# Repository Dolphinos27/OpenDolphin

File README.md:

# OpenDolphin
🐬 OpenDolphin: An open-source, DIY PCB clone of Flipper Zero.

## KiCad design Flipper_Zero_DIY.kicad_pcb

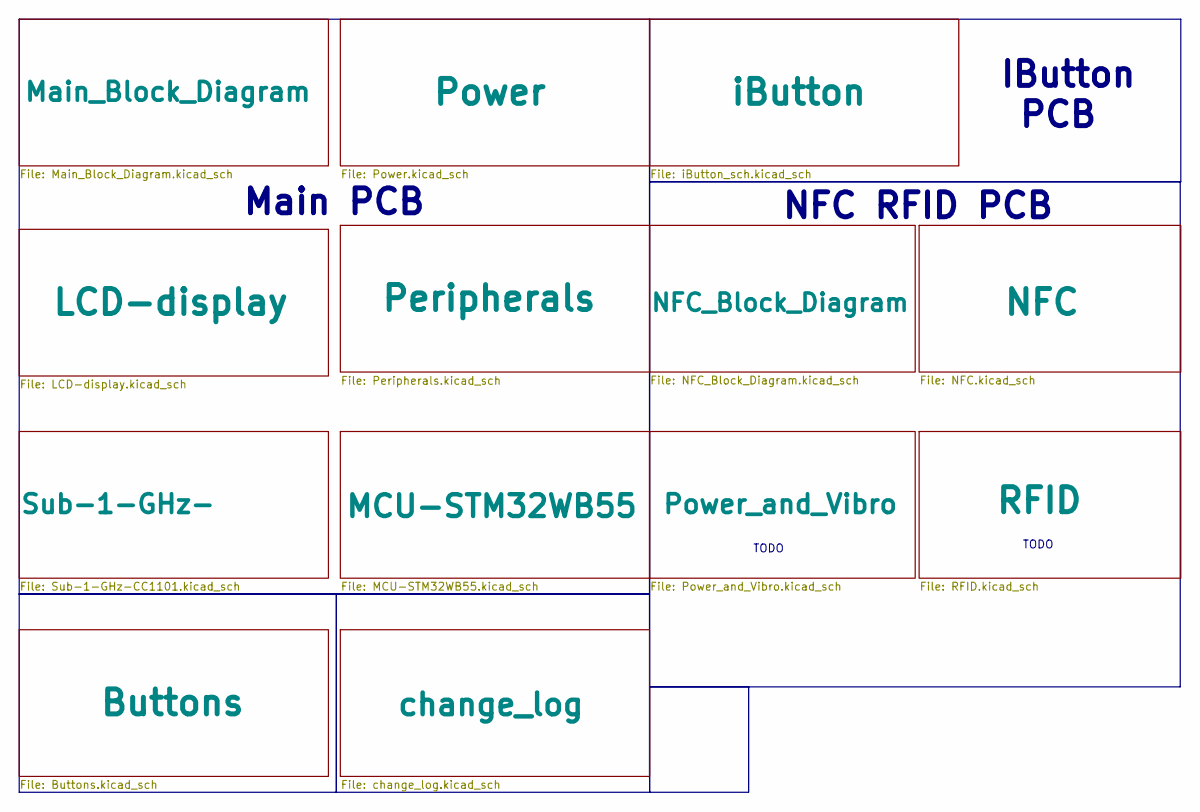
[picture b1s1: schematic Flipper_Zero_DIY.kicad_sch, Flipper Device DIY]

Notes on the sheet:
TODO
IButton PCB
Main PCB
NFC RFID PCB

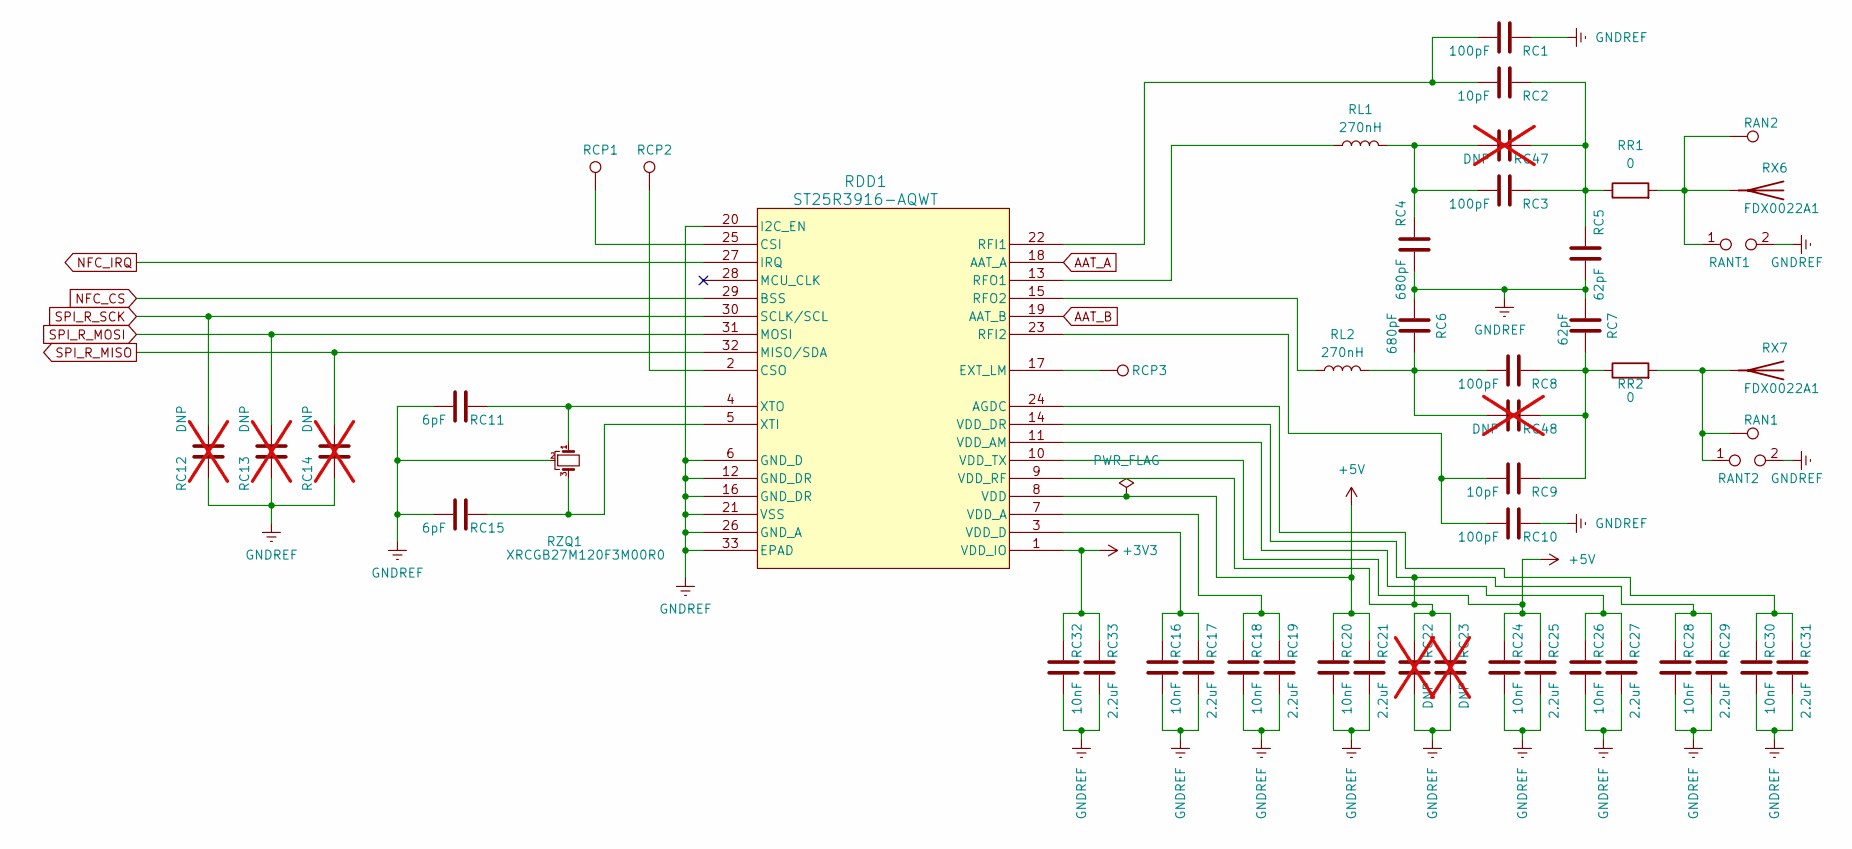
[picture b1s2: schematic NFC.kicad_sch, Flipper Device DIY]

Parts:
RC1, RC3, RC8, RC10: 100pF; C_0603_1608Metric
RC2, RC9: 10pF; C_0603_1608Metric
RC4, RC6: 680pF; C_0603_1608Metric
RC5, RC7: 62pF; C_0603_1608Metric
RC11, RC15: 6pF; C_0603_1608Metric
RC12, RC13, RC14, RC22, RC23, RC47, RC48: DNP; C_0603_1608Metric; not fitted
RC16, RC18, RC20, RC24, RC26, RC28, RC30, RC32: 10nF; C_0603_1608Metric
RC17, RC19, RC21, RC25, RC27, RC29, RC31, RC33: 2.2uF; C_0603_1608Metric
RDD1: ST25R3916-AQWT; VFQFPN32_5X5_WETTABLE_STM
RL1, RL2: 270nH; L_0603_1608Metric
RR1, RR2: 0; R_0603_1608Metric
RX6, RX7: FDX0022A1; R_0603_1608Metric
RZQ1: XRCGB27M120F3M00R0; Crystal_SMD_3225-4Pin_3.2x2.5mm
TP62: RCP1; TestPoint_Pad_D1.0mm
TP63: RCP2; TestPoint_Pad_D1.0mm
TP64: RAN2; TestPoint_Pad_D1.0mm
TP65: RANT1; SolderJumper-2_P1.3mm_Open_RoundedPad1.0x1.5mm
TP66: RAN1; TestPoint_Pad_D1.0mm
TP67: RANT2; SolderJumper-2_P1.3mm_Open_RoundedPad1.0x1.5mm
TP68: RCP3; TestPoint_Pad_D1.0mm

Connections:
+5V: RC20.2, RC21.2, RC24.2, RC25.2, RDD1.8 (VDD), RDD1.10 (VDD_TX); also elsewhere on the board
AAT_A: RDD1.18 (AAT_A)
AAT_B: RDD1.19 (AAT_B)
GND: RC1.2, RC4.1, RC5.1, RC6.2, RC7.2, RC10.2, RC11.1, RC12.2, RC13.2, RC14.2, RC15.1, RC16.1, RC17.1, RC18.1, RC19.1, RC20.1, RC21.1, RC22.1, RC23.1, RC24.1, RC25.1, RC26.1, RC27.1, RC28.1, RC29.1, RC30.1, RC31.1, RC32.1, RC33.1, RDD1.6 (GND_D), RDD1.12 (GND_DR), RDD1.16 (GND_DR), RDD1.20 (I2C_EN), RDD1.21 (VSS), RDD1.26 (GND_A), RDD1.33 (EPAD), RZQ1.2, TP65.2, TP67.2; also elsewhere on the board
NFC_CS: RDD1.29 (BSS); also elsewhere on the board
NFC_IRQ: RDD1.27 (IRQ)
unnamed: RC2.2, RC3.2, RC5.2, RC47.2, RR1.1
unnamed: RC3.1, RC4.2, RC47.1, RL1.2
unnamed: RC6.1, RC8.1, RC48.1, RL2.2
unnamed: RC7.1, RC8.2, RC9.2, RC48.2, RR2.1
unnamed: RC30.2, RC31.2, RDD1.24 (AGDC)
unnamed: RDD1.25 (CSI), TP62.1
unnamed: RDD1.2 (CSO), TP63.1
unnamed: RDD1.17 (EXT_LM), TP68.1
unnamed: RC1.1, RC2.1, RDD1.22 (RFI1)
unnamed: RC9.1, RC10.1, RDD1.23 (RFI2)
unnamed: RDD1.13 (RFO1), RL1.1
unnamed: RDD1.15 (RFO2), RL2.1
unnamed: RC18.2, RC19.2, RDD1.7 (VDD_A)
unnamed: RC26.2, RC27.2, RDD1.11 (VDD_AM)
unnamed: RC16.2, RC17.2, RDD1.3 (VDD_D)
unnamed: RC22.2, RC23.2, RC28.2, RC29.2, RDD1.9 (VDD_RF), RDD1.14 (VDD_DR)
unnamed: RC15.2, RDD1.5 (XTI), RZQ1.3
unnamed: RC11.2, RDD1.4 (XTO), RZQ1.1
unnamed: RR1.2, RX6.1 (A), TP64.1, TP65.1
unnamed: RR2.2, RX7.1 (A), TP66.1, TP67.1
SPI_R_MISO: RC14.1, RDD1.32 (MISO/SDA); also elsewhere on the board
SPI_R_MOSI: RC13.1, RDD1.31 (MOSI); also elsewhere on the board
SPI_R_SCK: RC12.1, RDD1.30 (SCLK/SCL); also elsewhere on the board

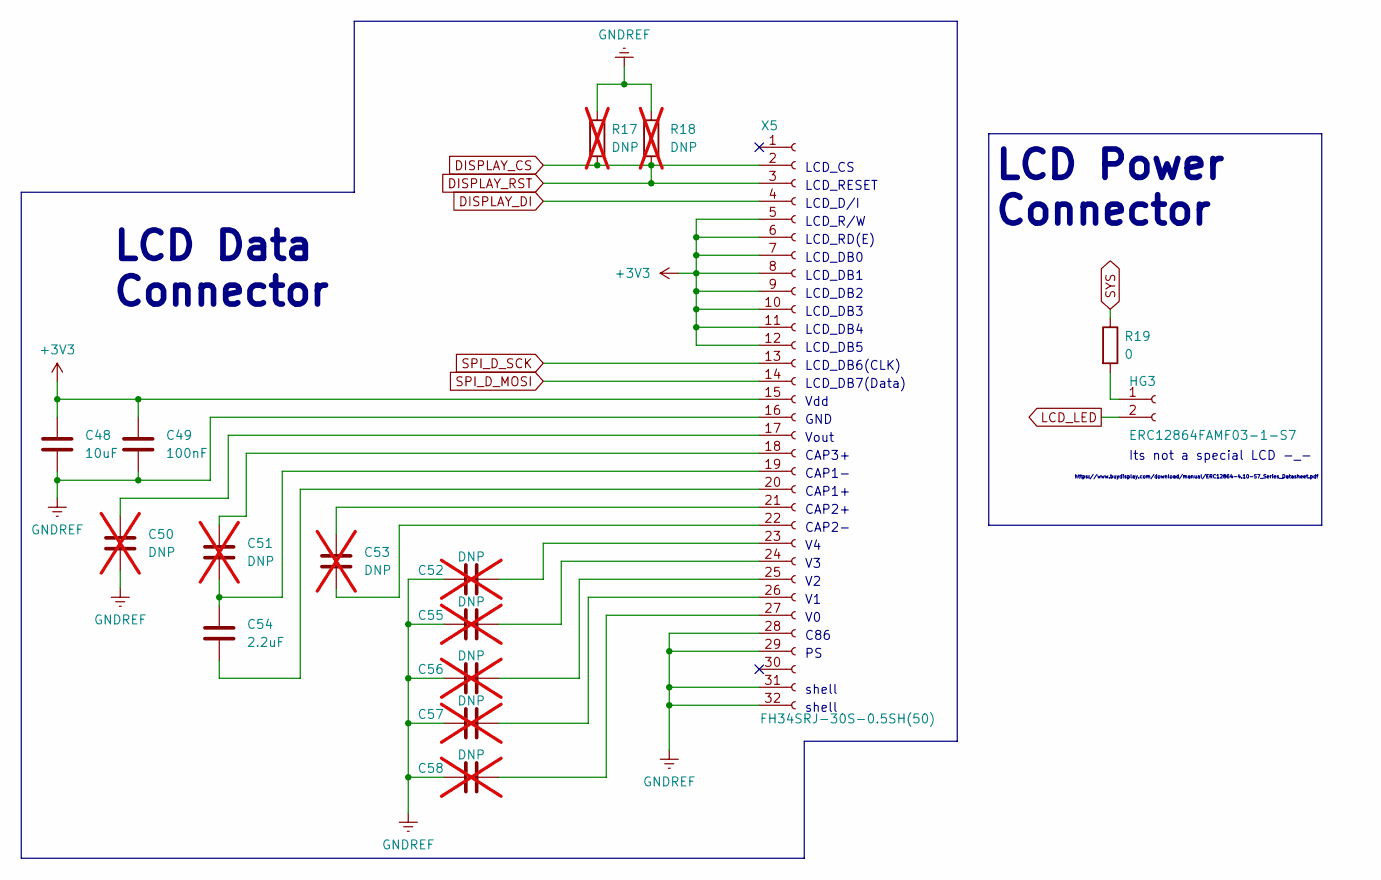
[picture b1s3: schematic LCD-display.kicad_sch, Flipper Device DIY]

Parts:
C48: 10uF; C_0603_1608Metric
C49: 100nF; C_0402_1005Metric
C50, C51, C52, C53, C55, C56, C57, C58: DNP; C_0402_1005Metric; not fitted
C54: 2.2uF; C_0402_1005Metric
HG3: ERC12864FAMF03-1-S7; PinHeader_1x02_P2.00mm_Vertical_SMD_Pin1Left
R17, R18: DNP; R_0402_1005Metric; not fitted
R19: 0; R_0402_1005Metric
X5: FH34SRJ-30S-0.5SH(50); CONN30x1_FH34SRJ-30S-0.5SH50_HIR

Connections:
DISPLAY_CS: R17.2, R18.2, X5.2, X5.3; also elsewhere on the board
DISPLAY_DI: X5.4; also elsewhere on the board
GND: C48.2, C49.2, C50.2, C52.1, C55.1, C56.1, C57.1, C58.1, R17.1, R18.1, X5.16, X5.28, X5.29, X5.31, X5.32; also elsewhere on the board
LCD_LED: HG3.2; also elsewhere on the board
unnamed: HG3.1, R19.2
unnamed: C50.1, X5.17
unnamed: C51.1, X5.18
unnamed: C51.2, C54.1, X5.19
unnamed: C54.2, X5.20
unnamed: C53.1, X5.21
unnamed: C53.2, X5.22
unnamed: C52.2, X5.23
unnamed: C55.2, X5.24
unnamed: C56.2, X5.25
unnamed: C57.2, X5.26
unnamed: C58.2, X5.27
SPI_D_MOSI: X5.13, X5.14; also elsewhere on the board
SYS: R19.1; also elsewhere on the board

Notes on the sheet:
LCD_DB2
LCD_D/I
LCD_DB0
LCD_RESET
LCD Data Connector
Vdd
LCD_DB6(CLK)
C86
GND
LCD_DB7(Data)
LCD_RD(E)
LCD_DB1
CAP1+
LCD_CS
CAP2-
shell
Vout
LCD_R/W
Its not a special LCD -_-
CAP3+
LCD Power Connector
CAP1-
https://www.buydisplay.com/download/manual/ERC12864-4.10-S7_Series_Datasheet.pdf
LCD_DB4
CAP2+
LCD_DB5
LCD_DB3

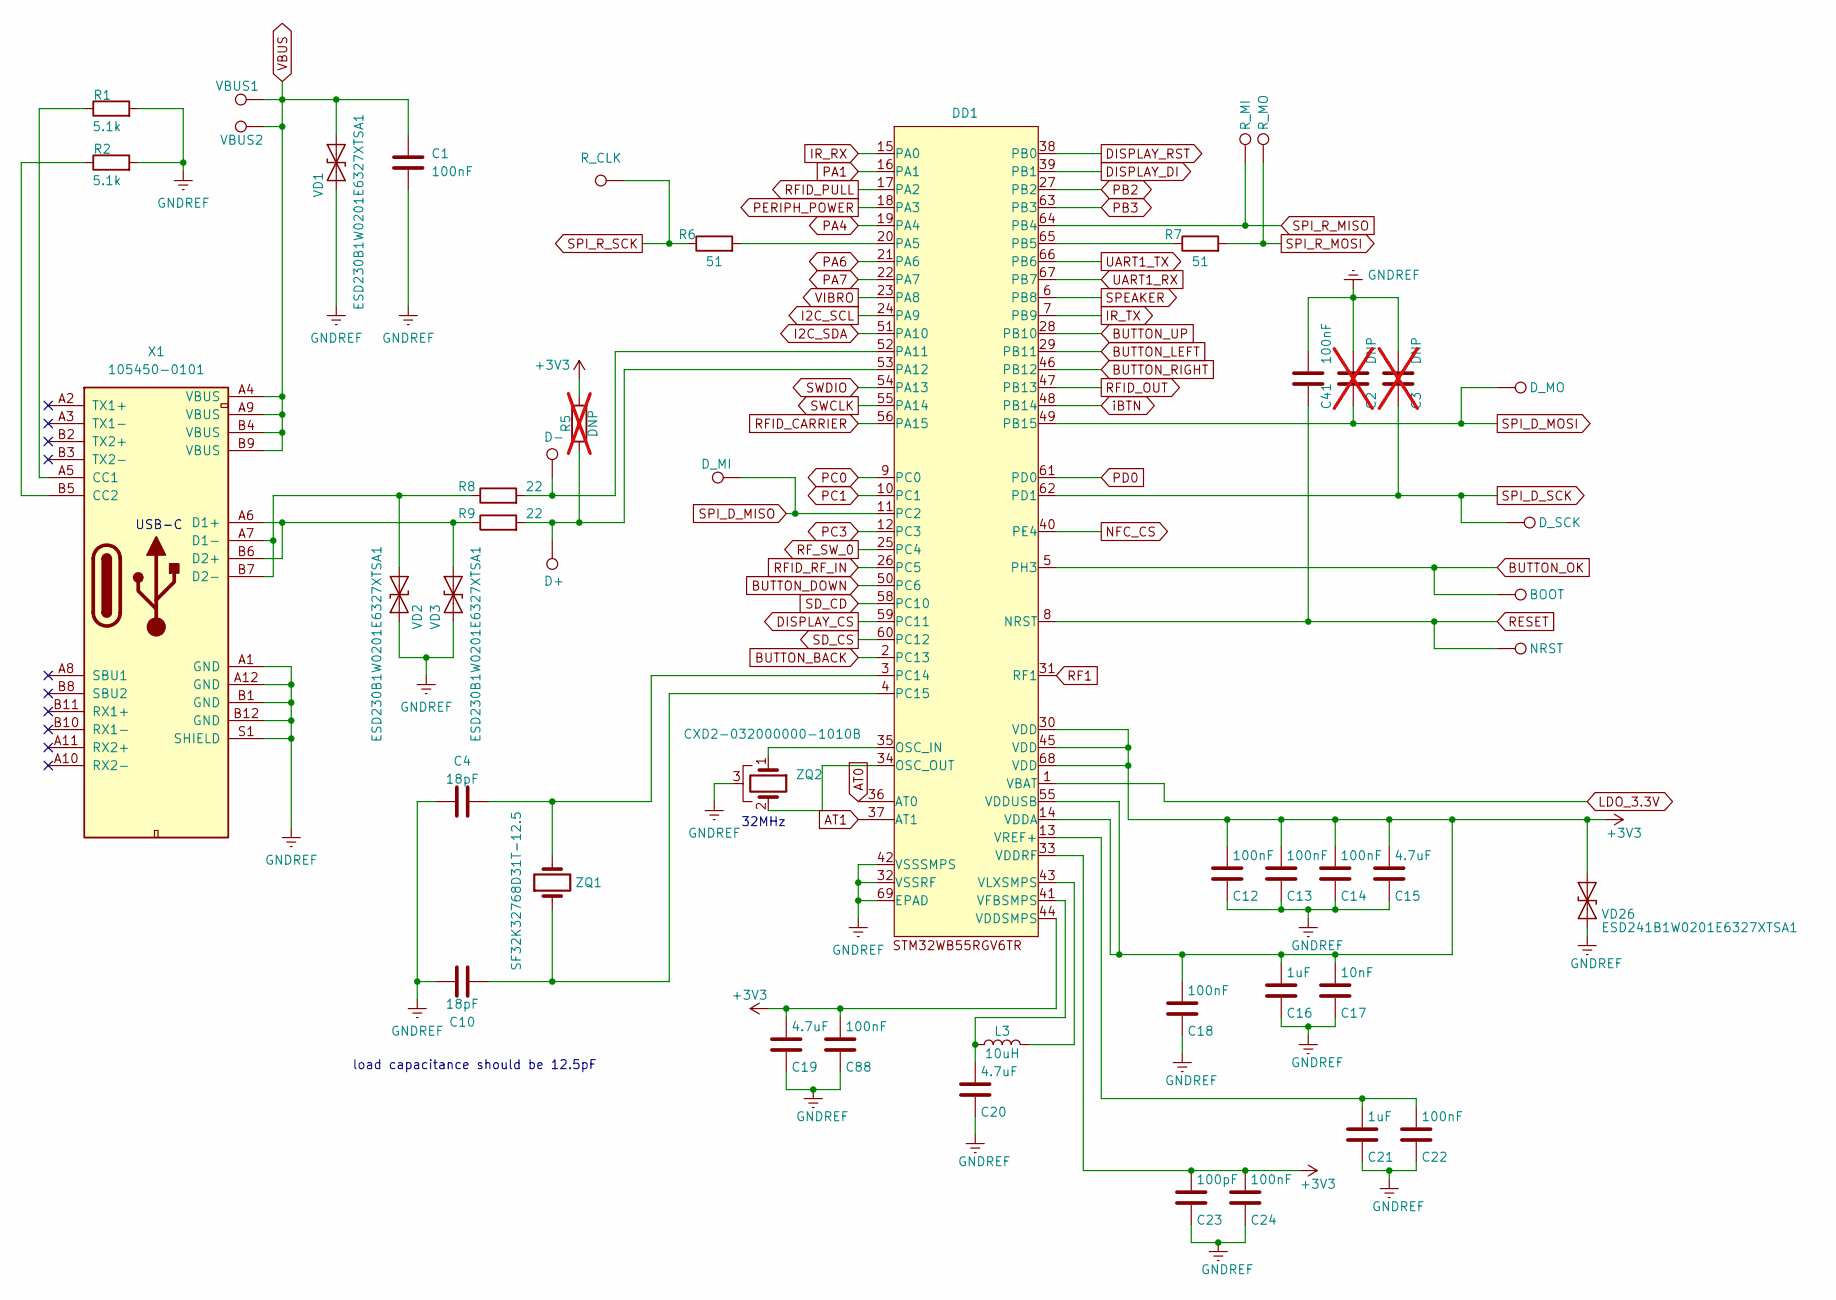
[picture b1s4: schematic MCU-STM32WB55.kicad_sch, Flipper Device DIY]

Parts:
C1, C12, C13, C14, C18, C22, C24, C88: 100nF; C_0402_1005Metric
C2, C3: DNP; C_0402_1005Metric; not fitted
C4, C10: 18pF; C_0402_1005Metric
C15, C19, C20: 4.7uF; C_0402_1005Metric
C16, C21: 1uF; C_0402_1005Metric
C17: 10nF; C_0402_1005Metric
C23: 100pF; C_0402_1005Metric
C41: 100nF; C_0603_1608Metric
DD1: STM32WB55RGV6TR
L3: 10uH; L_0805_2012Metric
R1, R2: 5.1k; R_0402_1005Metric
R5: DNP; R_0402_1005Metric; not fitted
R6, R7: 51; R_0402_1005Metric
R8, R9: 22; R_0402_1005Metric
TP40: R_CLK; TestPoint_Pad_1.0x1.0mm
TP41: VBUS1; TestPoint_Pad_1.0x1.0mm
TP42: VBUS2; TestPoint_Pad_1.0x1.0mm
TP43: D-; TestPoint_Pad_1.0x1.0mm
TP44: D+; TestPoint_Pad_1.0x1.0mm
TP45: D_MI; TestPoint_Pad_1.0x1.0mm
TP46: R_MI; TestPoint_Pad_1.0x1.0mm
TP47: R_MO; TestPoint_Pad_1.0x1.0mm
TP48: D_MO; TestPoint_Pad_1.0x1.0mm
TP49: D_SCK; TestPoint_Pad_1.0x1.0mm
TP50: BOOT; TestPoint_Pad_1.0x1.0mm
TP51: NRST; TestPoint_Pad_1.0x1.0mm
VD1, VD2, VD3: ESD230B1W0201E6327XTSA1; D_0201_0603Metric
VD26: ESD241B1W0201E6327XTSA1; D_0201_0603Metric
X1: 105450-0101; USB_C_Receptacle_Amphenol_12401610E4-2A
ZQ1: SF32K32768D31T-12.5; Crystal_SMD_3215-2Pin_3.2x1.5mm
ZQ2: CXD2-032000000-1010B; Crystal_SMD_2520-4Pin_2.5x2.0mm

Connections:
AT0: DD1.36 (AT0)
AT1: DD1.37 (AT1)
BUTTON_BACK: DD1.2 (PC13); also elsewhere on the board
BUTTON_DOWN: DD1.50 (PC6); also elsewhere on the board
BUTTON_LEFT: DD1.29 (PB11); also elsewhere on the board
BUTTON_OK: DD1.5 (PH3), TP50.1; also elsewhere on the board
BUTTON_RIGHT: DD1.46 (PB12); also elsewhere on the board
BUTTON_UP: DD1.28 (PB10); also elsewhere on the board
DISPLAY_CS: DD1.38 (PB0), DD1.59 (PC11); also elsewhere on the board
DISPLAY_DI: DD1.39 (PB1); also elsewhere on the board
GND: C1.2, C2.1, C3.1, C4.1, C10.1, C12.2, C13.2, C14.2, C15.2, C16.2, C17.2, C18.2, C19.2, C20.2, C21.2, C22.2, C23.2, C24.2, C41.1, C88.2, DD1.32 (VSSRF), DD1.42 (VSSSMPS), DD1.69 (EPAD), R1.2, R2.2, VD1.1 (A1), VD2.1 (A1), VD3.1 (A1), VD26.1 (A1), X1.A1 (GND), X1.A12 (GND), X1.B1 (GND), X1.B12 (GND), X1.S1 (SHIELD), ZQ2.3; also elsewhere on the board
I2C_SCL: DD1.24 (PA9); also elsewhere on the board
I2C_SDA: DD1.51 (PA10); also elsewhere on the board
IR_RX: DD1.15 (PA0); also elsewhere on the board
IR_TX: DD1.7 (PB9); also elsewhere on the board
LDO_3.3V: DD1.1 (VBAT); also elsewhere on the board
NFC_CS: DD1.40 (PE4); also elsewhere on the board
unnamed: DD1.35 (OSC_IN), ZQ2.1
unnamed: DD1.34 (OSC_OUT), ZQ2.2
unnamed: DD1.20 (PA5), R6.2
unnamed: DD1.52 (PA11), R8.2, TP43.1
unnamed: DD1.53 (PA12), R5.1, R9.2, TP44.1
unnamed: DD1.65 (PB5), R7.1
unnamed: C4.2, DD1.3 (PC14), ZQ1.2
unnamed: C10.2, DD1.4 (PC15), ZQ1.1
unnamed: C20.1, DD1.41 (VFBSMPS), L3.1
unnamed: DD1.43 (VLXSMPS), L3.2
unnamed: C21.1, C22.1, DD1.13 (VREF+)
unnamed: R8.1, VD2.2 (A2), X1.A7 (D1-), X1.B7 (D2-)
unnamed: R9.1, VD3.2 (A2), X1.A6 (D1+), X1.B6 (D2+)
unnamed: R1.1, X1.A5 (CC1)
unnamed: R2.1, X1.B5 (CC2)
PA1: DD1.16 (PA1)
PA4: DD1.19 (PA4); also elsewhere on the board
PA6: DD1.21 (PA6); also elsewhere on the board
PA7: DD1.22 (PA7)
PB2: DD1.27 (PB2)
PB3: DD1.63 (PB3)
PC0: DD1.9 (PC0)
PC1: DD1.10 (PC1)
PC3: DD1.12 (PC3)
PD0: DD1.61 (PD0)
PERIPH_POWER: DD1.18 (PA3); also elsewhere on the board
RESET: C41.2, DD1.8 (NRST), TP51.1; also elsewhere on the board
RF1: DD1.31 (RF1)
RFID_CARRIER: DD1.56 (PA15); also elsewhere on the board
RFID_OUT: DD1.47 (PB13); also elsewhere on the board
RFID_PULL: DD1.17 (PA2); also elsewhere on the board
RFID_RF_IN: DD1.26 (PC5); also elsewhere on the board
RF_SW_0: DD1.25 (PC4)
SD_CD: DD1.58 (PC10); also elsewhere on the board
SD_CS: DD1.60 (PC12); also elsewhere on the board
SPEAKER: DD1.6 (PB8); also elsewhere on the board
SPI_D_MISO: DD1.11 (PC2), TP45.1; also elsewhere on the board
SPI_D_MOSI: C2.2, C3.2, DD1.49 (PB15), DD1.62 (PD1), TP48.1, TP49.1; also elsewhere on the board
SPI_R_MISO: DD1.64 (PB4), TP46.1; also elsewhere on the board
SPI_R_MOSI: R7.2, TP47.1; also elsewhere on the board
SPI_R_SCK: R6.1, TP40.1; also elsewhere on the board
SWDIO: DD1.54 (PA13)
UART1_RX: DD1.67 (PB7)
UART1_TX: DD1.66 (PB6)
VBUS: C1.1, TP41.1, TP42.1, VD1.2 (A2), X1.A4 (VBUS), X1.A9 (VBUS), X1.B4 (VBUS), X1.B9 (VBUS); also elsewhere on the board
VIBRO: DD1.23 (PA8); also elsewhere on the board
iBTN: DD1.48 (PB14); also elsewhere on the board

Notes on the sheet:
load capacitance should be 12.5pF
32MHz
USB-C

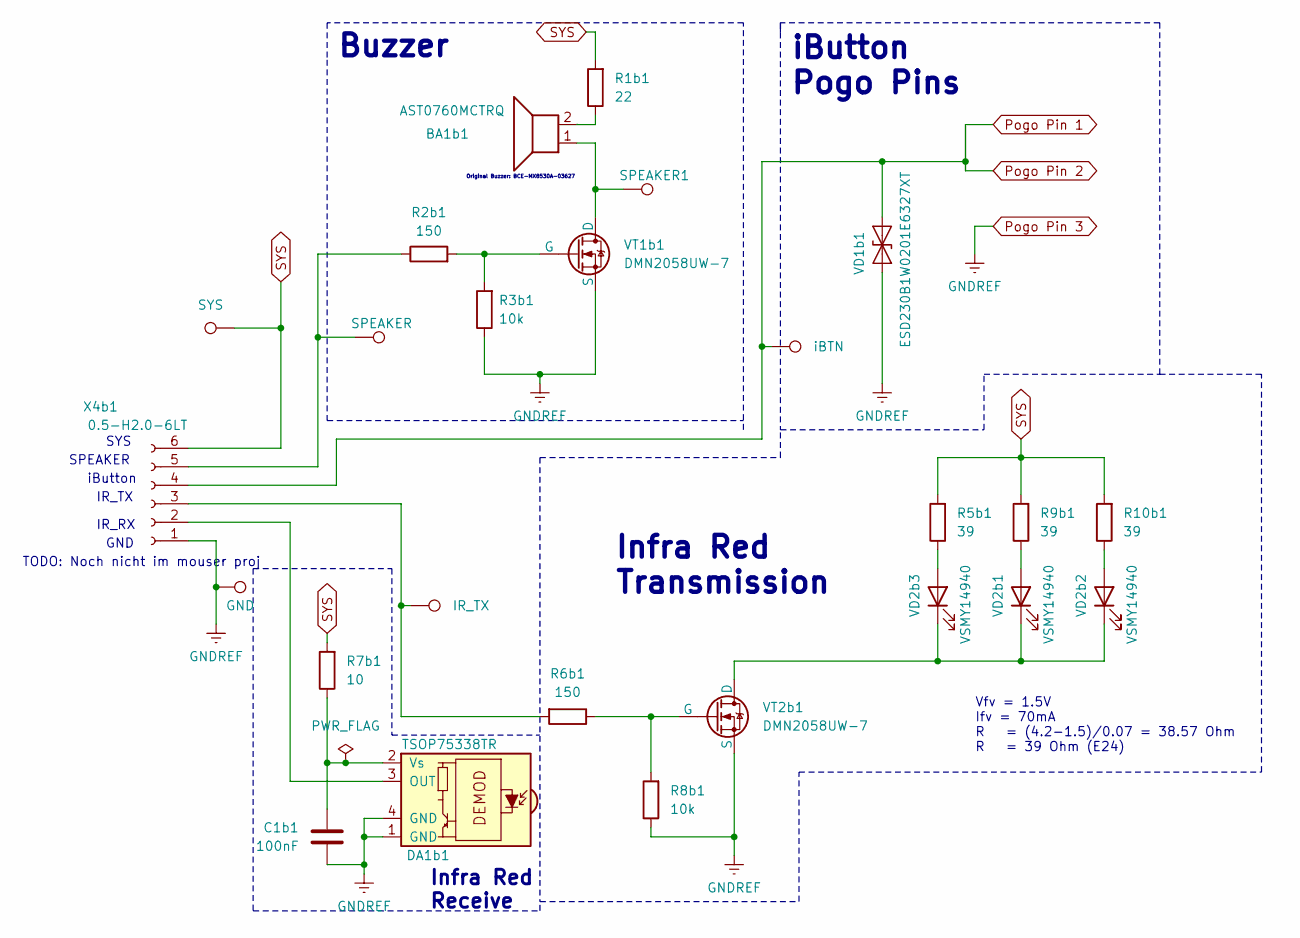
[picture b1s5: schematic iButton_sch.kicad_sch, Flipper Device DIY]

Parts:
BA1b1: AST0760MCTRQ; Buzzer_539-AST0760MCTRQ
C1b1: 100nF; C_0402_1005Metric
DA1b1: TSOP75338TR
R1b1: 22; R_0603_1608Metric
R2b1, R6b1: 150; R_0402_1005Metric
R3b1, R8b1: 10k; R_0402_1005Metric
R5b1, R9b1, R10b1: 39; R_0402_1005Metric
R7b1: 10; R_0402_1005Metric
TP56: SYS; TestPoint_Pad_1.0x1.0mm
TP57: SPEAKER; TestPoint_Pad_1.0x1.0mm
TP58: SPEAKER1; TestPoint_Pad_1.0x1.0mm
TP59: iBTN; TestPoint_Pad_1.0x1.0mm
TP60: IR_TX; TestPoint_Pad_1.0x1.0mm
TP61: GND; TestPoint_Pad_1.0x1.0mm
VD1b1: ESD230B1W0201E6327XT; D_SOD-923
VD2b1, VD2b2, VD2b3: VSMY14940; LED_0603_1608Metric
VT1b1, VT2b1: DMN2058UW-7; SOT323_DMN2058UW_DIO
X4b1: 0.5-H2.0-6LT; JST_SH_SM06B-SRSS-TB_1x06-1MP_P1.00mm_Horizontal

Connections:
GND: C1b1.2, DA1b1.1 (GND), DA1b1.4 (GND), R3b1.1, R8b1.1, TP61.1, VD1b1.1 (A1), VT1b1.3 (S), VT2b1.3 (S), X4b1.1; also elsewhere on the board
unnamed: BA1b1.2, R1b1.1
unnamed: DA1b1.3 (OUT), X4b1.2
unnamed: C1b1.1, DA1b1.2 (Vs), R7b1.1
unnamed: R9b1.1, VD2b1.2 (A)
unnamed: VD2b1.1 (K), VD2b2.1 (K), VD2b3.1 (K), VT2b1.1 (D)
unnamed: R10b1.1, VD2b2.2 (A)
unnamed: R5b1.1, VD2b3.2 (A)
unnamed: BA1b1.1, TP58.1, VT1b1.1 (D)
unnamed: R2b1.2, R3b1.2, VT1b1.2 (G)
unnamed: R6b1.1, R8b1.2, VT2b1.2 (G)
unnamed: R6b1.2, TP60.1, X4b1.3
unnamed: R2b1.1, TP57.1, X4b1.5
Pogo Pin 1: TP59.1, VD1b1.2 (A2), X4b1.4
SYS: R1b1.2, R5b1.2, R7b1.2, R9b1.2, R10b1.2, TP56.1, X4b1.6; also elsewhere on the board

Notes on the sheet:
GND
iButton
IR_RX
Infra Red Transmission
Buzzer
SYS
IR_TX
SPEAKER
iButton Pogo Pins
Vfv = 1.5V Ifv = 70mA R = (4.2-1.5)/0.07 = 38.57 Ohm R = 39 Ohm (E24)
Original Buzzer: BCE-MX8530A-03627
TODO: Noch nicht im mouser proj
Infra Red Receive

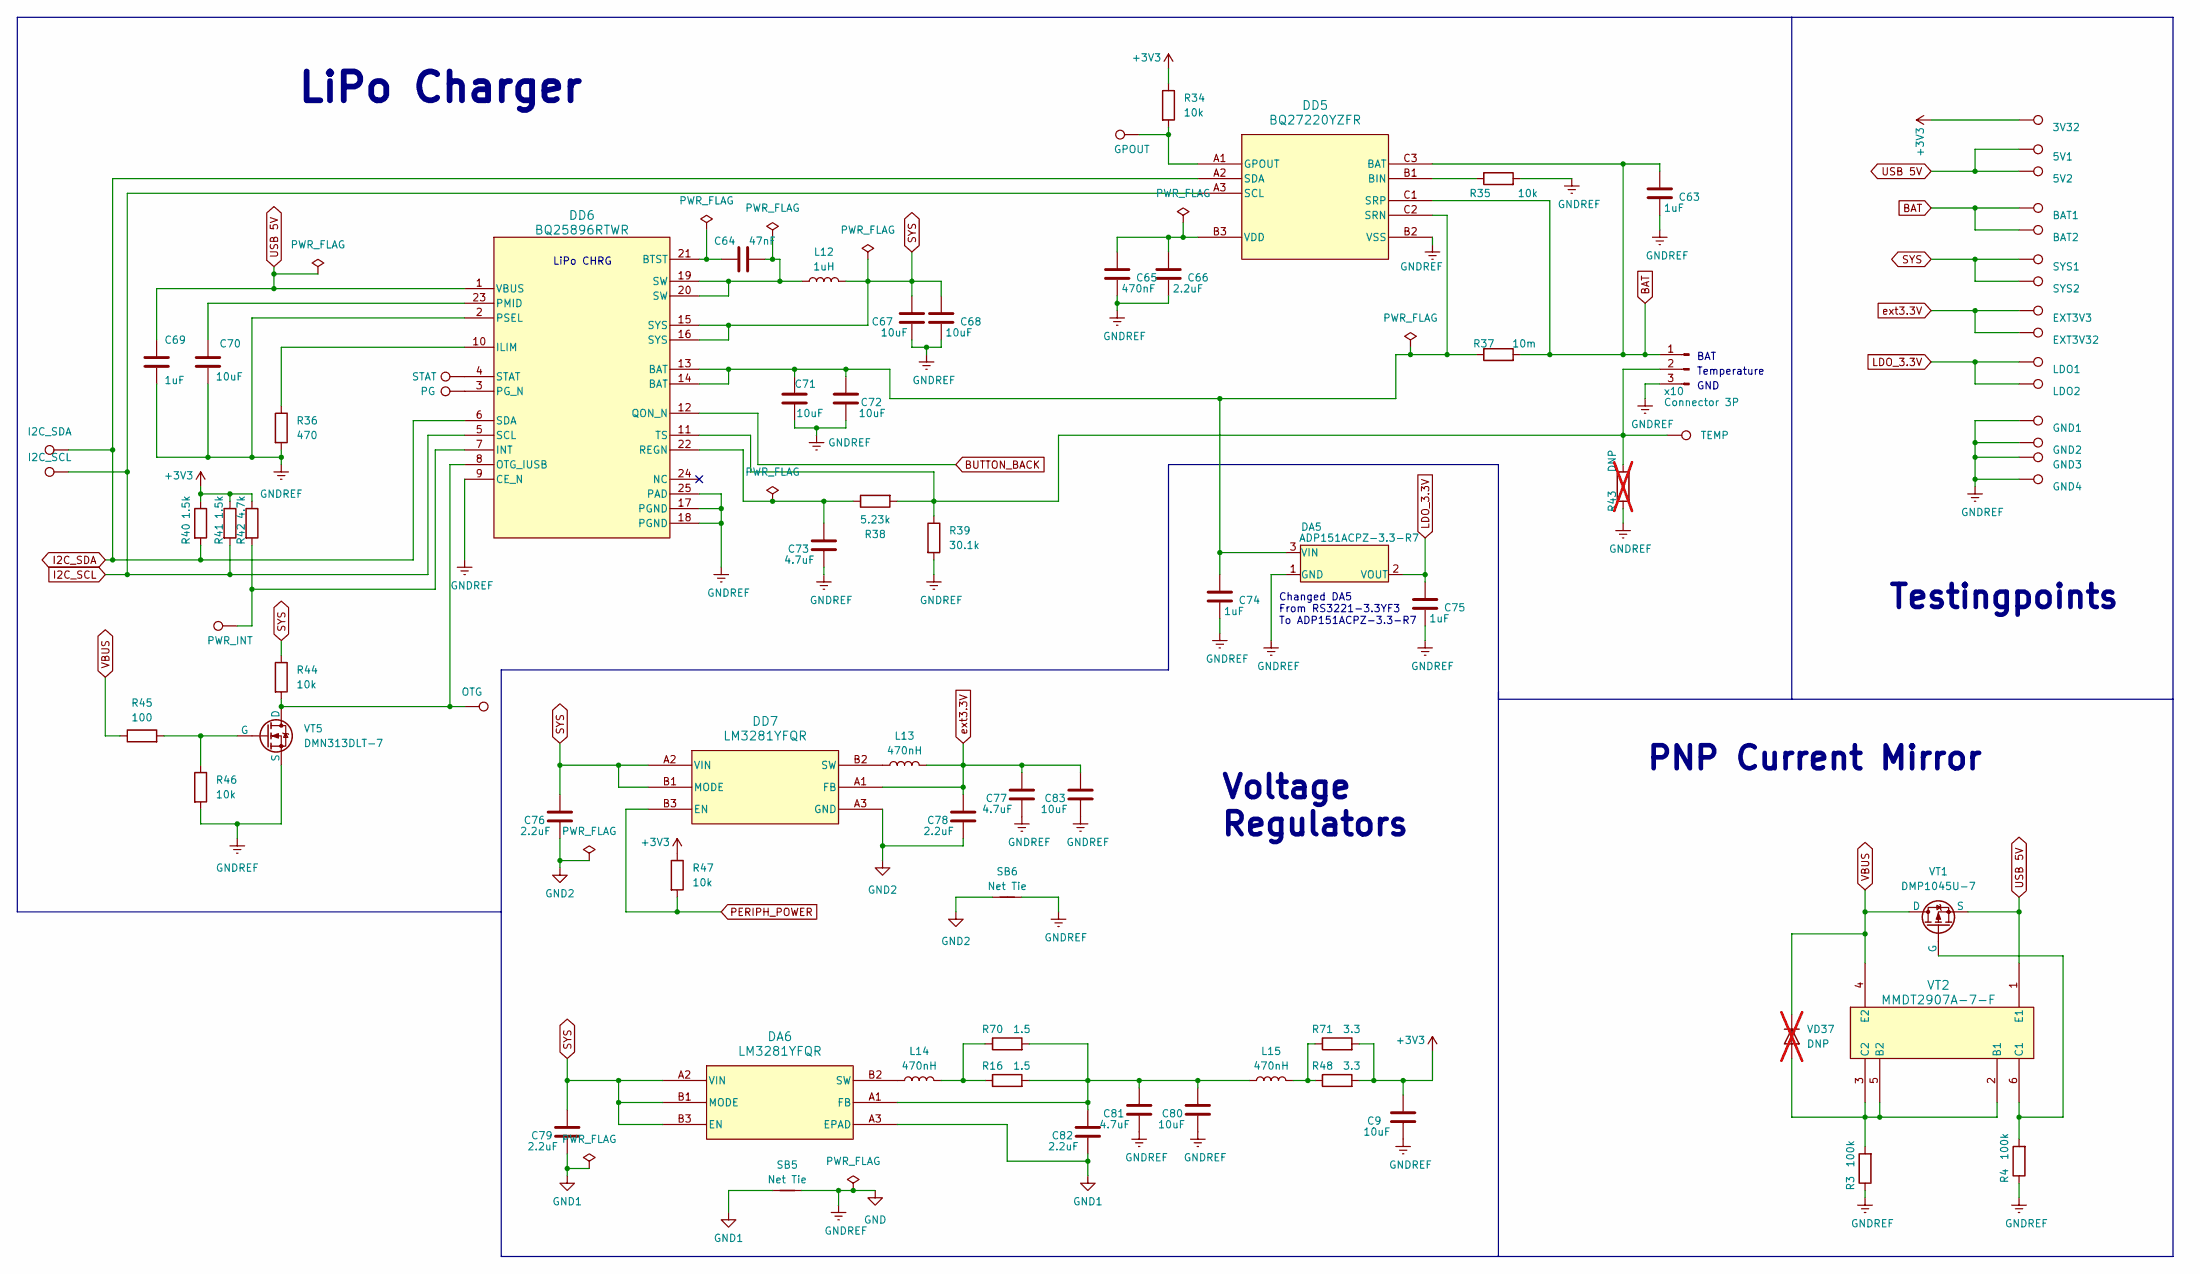
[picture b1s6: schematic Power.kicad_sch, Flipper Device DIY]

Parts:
C9, C80, C83: 10uF; C_0402_1005Metric
C63, C74, C75: 1uF; C_0402_1005Metric
C64: 47nF; C_0402_1005Metric
C65: 470nF; C_0402_1005Metric
C66, C76, C78, C79, C82: 2.2uF; C_0402_1005Metric
C67, C68, C70, C71, C72: 10uF; C_0603_1608Metric
C69: 1uF; C_0603_1608Metric
C73, C77, C81: 4.7uF; C_0402_1005Metric
DA5: ADP151ACPZ-3.3-R7; LFCSP-6-1EP_2x2mm_P0.65mm_EP1x1.6mm
DA6: LM3281YFQR
DD5: BQ27220YZFR
DD6: BQ25896RTWR
DD7: LM3281YFQR
L12: 1uH; L_TDK_NLV25_2.5x2.0mm
L13, L14, L15: 470nH; L_0805_2012Metric
R3: 100k; C_0402_1005Metric
R4: 100k; R_0402_1005Metric
R16, R70: 1.5; R_0402_1005Metric
R34, R35, R44, R46, R47: 10k; R_0402_1005Metric
R36: 470; R_0402_1005Metric
R37: 10m; R_2512_6332Metric
R38: 5.23k; R_0402_1005Metric
R39: 30.1k; R_0402_1005Metric
R40, R41: 1.5k; R_0402_1005Metric
R42: 4.7k; R_0402_1005Metric
R43: DNP; R_0402_1005Metric; not fitted
R45: 100; R_0402_1005Metric
R48, R71: 3.3; R_0402_1005Metric
SB5, SB6: Net Tie; NetTie-2_SMD_Pad0.5mm
TP1: STAT; TestPoint_Pad_1.0x1.0mm
TP2: PG; TestPoint_Pad_1.0x1.0mm
TP3: PWR_INT; TestPoint_Pad_1.0x1.0mm
TP4: OTG; TestPoint_Pad_1.0x1.0mm
TP5: GPOUT; TestPoint_Pad_1.0x1.0mm
TP6: TEMP; TestPoint_Pad_1.0x1.0mm
TP7: 3V32; TestPoint_Pad_1.0x1.0mm
TP8: 5V1; TestPoint_Pad_1.0x1.0mm
TP9: 5V2; TestPoint_Pad_1.0x1.0mm
TP10: BAT1; TestPoint_Pad_1.0x1.0mm
TP11: BAT2; TestPoint_Pad_1.0x1.0mm
TP12: SYS1; TestPoint_Pad_1.0x1.0mm
TP13: SYS2; TestPoint_Pad_1.0x1.0mm
TP14: EXT3V3; TestPoint_Pad_1.0x1.0mm
TP15: EXT3V32; TestPoint_Pad_1.0x1.0mm
TP16: LDO1; TestPoint_Pad_1.0x1.0mm
TP17: LDO2; TestPoint_Pad_1.0x1.0mm
TP18: GND1; TestPoint_Pad_1.0x1.0mm
TP19: GND2; TestPoint_Pad_1.0x1.0mm
TP20: GND3; TestPoint_Pad_1.0x1.0mm
TP21: GND4; TestPoint_Pad_1.0x1.0mm
TP22: I2C_SDA; TestPoint_Pad_1.0x1.0mm
TP23: I2C_SCL; TestPoint_Pad_1.0x1.0mm
VD37: DNP; D_SOD-523; not fitted
VT1: DMP1045U-7; SOT-23-3
VT2: MMDT2907A-7-F; SOT-363_SC-70-6
VT5: DMN313DLT-7; SOT-523
x10: Connector 3P; PinHeader_1x03_P2.54mm_Horizontal

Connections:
BAT: C63.2, DD5.C1 (SRP), DD5.C3 (BAT), R37.2, TP10.1, TP11.1, x10.1
BUTTON_BACK: DD6.12 (QON_N); also elsewhere on the board
GND: C9.1, C63.1, C65.1, C66.1, C67.1, C68.1, C69.2, C70.2, C71.1, C72.1, C73.1, C74.1, C75.1, C77.1, C80.1, C81.1, C83.1, DA5.1 (GND), DD5.B2 (VSS), DD6.2 (PSEL), DD6.9 (CE_N), DD6.17 (PGND), DD6.18 (PGND), DD6.25 (PAD), R3.1, R4.1, R35.2, R36.2, R39.2, R43.1, R46.2, SB5.2, SB6.2, TP18.1, TP19.1, TP20.1, TP21.1, VT5.3 (S), x10.3; also elsewhere on the board
GND1: C79.1, C82.1, DA6.A3 (EPAD), SB5.1
GND2: C76.1, C78.1, DD7.A3 (GND), SB6.1
I2C_SCL: DD5.A3 (SCL), DD6.5 (SCL), R41.2, TP23.1; also elsewhere on the board
I2C_SDA: DD5.A2 (SDA), DD6.6 (SDA), R40.2, TP22.1; also elsewhere on the board
LDO_3.3V: C75.2, DA5.2 (VOUT), TP16.1, TP17.1; also elsewhere on the board
unnamed: C64.2, DD6.19 (SW), DD6.20 (SW), L12.1
unnamed: C71.2, C72.2, C74.2, DA5.3 (VIN), DD5.C2 (SRN), DD6.13 (BAT), DD6.14 (BAT), R37.1
unnamed: C80.2, C81.2, C82.2, DA6.A1 (FB), L15.1, R16.2, R70.2
unnamed: DA6.B2 (SW), L14.1
unnamed: DD5.B1 (BIN), R35.1
unnamed: DD5.A1 (GPOUT), R34.2, TP5.1
unnamed: C65.2, C66.2, DD5.B3 (VDD)
unnamed: C64.1, DD6.21 (BTST)
unnamed: DD6.10 (ILIM), R36.1
unnamed: DD6.7 (INT), R42.2, TP3.1
unnamed: DD6.8 (OTG_IUSB), R44.2, TP4.1, VT5.1 (D)
unnamed: DD6.3 (PG_N), TP2.1
unnamed: C70.1, DD6.23 (PMID)
unnamed: C73.2, DD6.22 (REGN), R38.1
unnamed: DD6.4 (STAT), TP1.1
unnamed: DD6.11 (TS), R38.2, R39.1, R43.2, TP6.1, x10.2
unnamed: DD7.B2 (SW), L13.1
unnamed: L14.2, R16.1, R70.1
unnamed: L15.2, R48.1, R71.1
unnamed: R3.2, VD37.2 (A), VT2.2 (B1), VT2.3 (C2), VT2.5 (B2)
unnamed: R4.2, VT1.2 (G), VT2.6 (C1)
unnamed: R45.2, R46.1, VT5.2 (G)
PERIPH_POWER: DD7.B3 (EN), R47.2; also elsewhere on the board
SYS: C67.2, C68.2, C76.2, C79.2, DA6.A2 (VIN), DA6.B1 (MODE), DA6.B3 (EN), DD6.15 (SYS), DD6.16 (SYS), DD7.A2 (VIN), DD7.B1 (MODE), L12.2, R44.1, TP12.1, TP13.1; also elsewhere on the board
USB 5V: C69.1, DD6.1 (VBUS), TP8.1, TP9.1, VT1.3 (S), VT2.1 (E1); also elsewhere on the board
VBUS: R45.1, VD37.1 (K), VT1.1 (D), VT2.4 (E2); also elsewhere on the board
ext3.3V: C77.2, C78.2, C83.2, DD7.A1 (FB), L13.2, TP14.1, TP15.1; also elsewhere on the board

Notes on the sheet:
LiPo CHRG
PNP Current Mirror
GND
BAT
Testingpoints
Changed DA5 From RS3221-3.3YF3 To ADP151ACPZ-3.3-R7
Voltage Regulators
LiPo Charger
Temperature

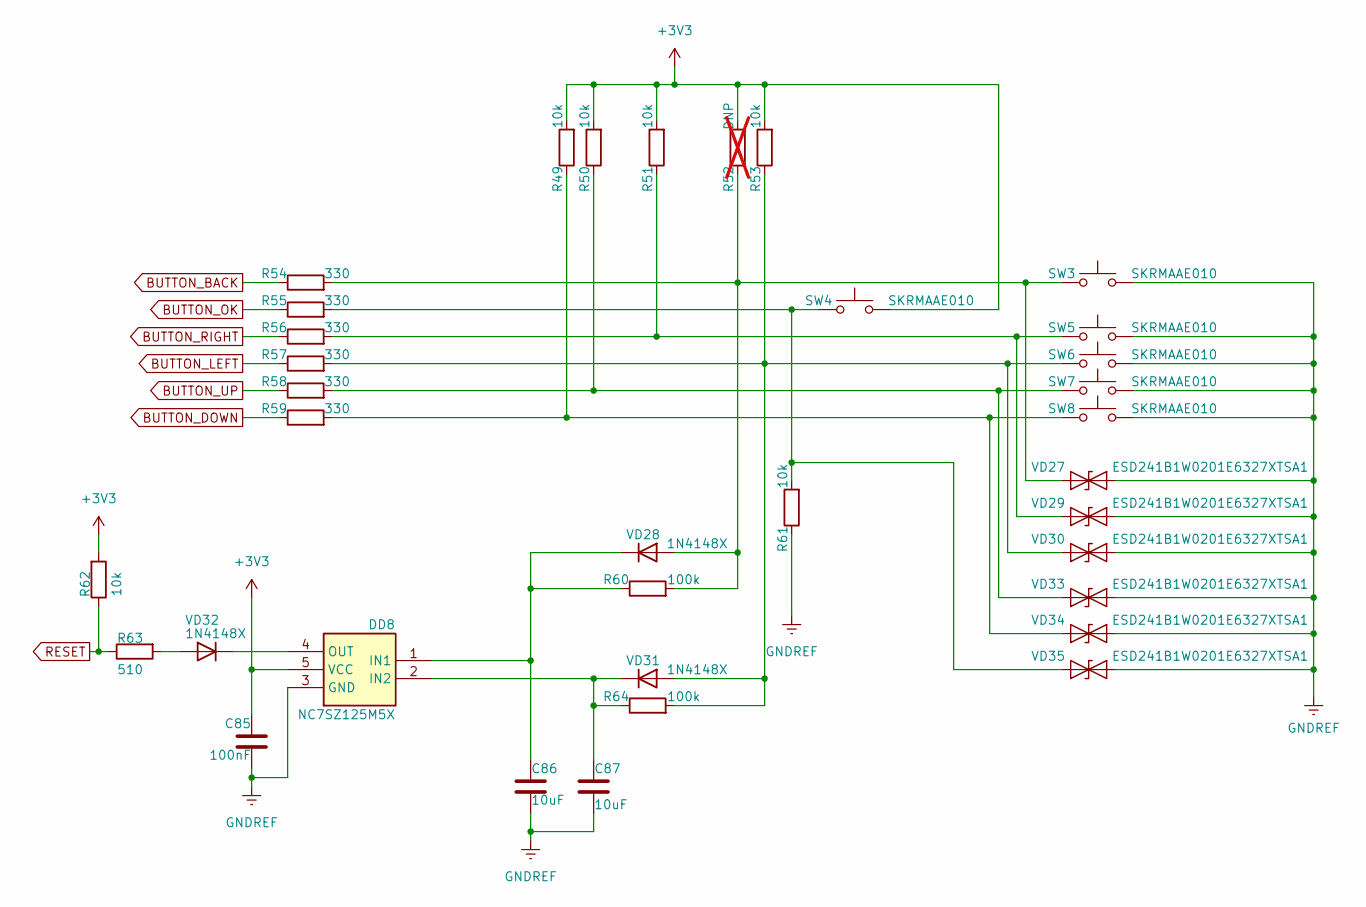
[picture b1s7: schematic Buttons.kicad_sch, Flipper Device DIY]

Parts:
C85: 100nF; C_0402_1005Metric
C86, C87: 10uF; C_0402_1005Metric
DD8: NC7SZ125M5X; SOT-23-5
R49, R50, R51, R53, R61, R62: 10k; R_0402_1005Metric
R52: DNP; R_0402_1005Metric; not fitted
R54, R55, R56, R57, R58, R59: 330; R_0402_1005Metric
R60, R64: 100k; R_0402_1005Metric
R63: 510; R_0402_1005Metric
SW3, SW4, SW5, SW6, SW7, SW8: SKRMAAE010; SKRMAAE010_AAL
VD27, VD29, VD30, VD33, VD34, VD35: ESD241B1W0201E6327XTSA1; D_0201_0603Metric
VD28, VD31, VD32: 1N4148X; D_SOD-523

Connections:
BUTTON_BACK: R54.1; also elsewhere on the board
BUTTON_DOWN: R59.1; also elsewhere on the board
BUTTON_LEFT: R57.1; also elsewhere on the board
BUTTON_OK: R55.1; also elsewhere on the board
BUTTON_RIGHT: R56.1; also elsewhere on the board
BUTTON_UP: R58.1; also elsewhere on the board
GND: C85.2, C86.2, C87.2, DD8.3 (GND), R61.1, SW3.2, SW5.2, SW6.2, SW7.2, SW8.2, VD27.2 (A2), VD29.2 (A2), VD30.2 (A2), VD33.2 (A2), VD34.2 (A2), VD35.2 (A2); also elsewhere on the board
unnamed: C86.1, DD8.1 (IN1), R60.1, VD28.1 (K)
unnamed: C87.1, DD8.2 (IN2), R64.1, VD31.1 (K)
unnamed: DD8.4 (OUT), VD32.1 (K)
unnamed: R52.1, R54.2, R60.2, SW3.1, VD27.1 (A1), VD28.2 (A)
unnamed: R51.1, R56.2, SW5.1, VD29.1 (A1)
unnamed: R53.1, R57.2, R64.2, SW6.1, VD30.1 (A1), VD31.2 (A)
unnamed: R63.2, VD32.2 (A)
unnamed: R50.1, R58.2, SW7.1, VD33.1 (A1)
unnamed: R49.1, R59.2, SW8.1, VD34.1 (A1)
unnamed: R55.2, R61.2, SW4.1, VD35.1 (A1)
RESET: R62.1, R63.1; also elsewhere on the board

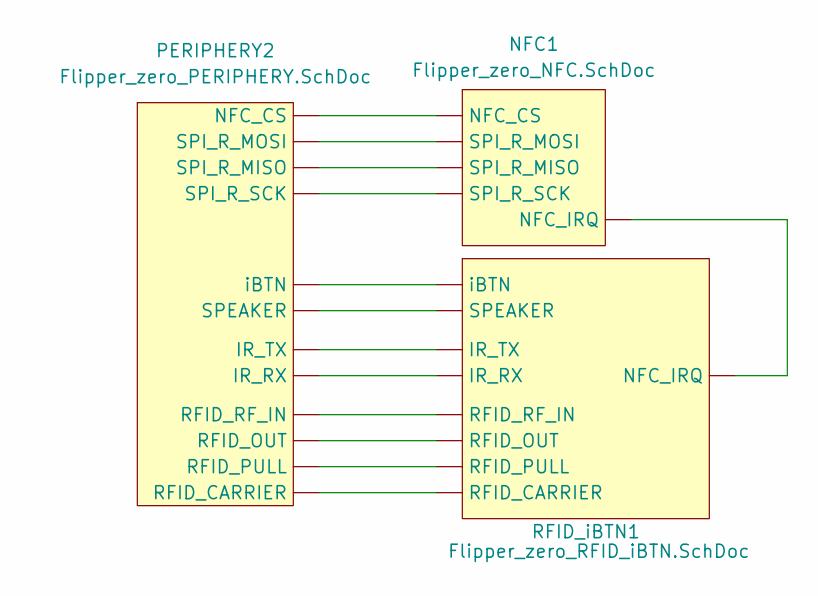
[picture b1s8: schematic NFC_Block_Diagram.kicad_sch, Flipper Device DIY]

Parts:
NFC1: Flipper_zero_NFC.SchDoc
PERIPHERY2: Flipper_zero_PERIPHERY.SchDoc
RFID_iBTN1: Flipper_zero_RFID_iBTN.SchDoc

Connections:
unnamed: NFC1., PERIPHERY2., RFID_iBTN1.
unnamed: PERIPHERY2., RFID_iBTN1.

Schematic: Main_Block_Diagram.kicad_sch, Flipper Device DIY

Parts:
Buttons1: (no value)
CC1101: (no value)
LCD1: (no value)
MCU1: (no value)
Periphery1: (no value)
Power1: (no value)

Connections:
unnamed: Buttons1., MCU1., Periphery1., Power1.
unnamed: CC1101., MCU1., Periphery1.
unnamed: LCD1., MCU1., Periphery1.
unnamed: MCU1., Periphery1., Power1.
